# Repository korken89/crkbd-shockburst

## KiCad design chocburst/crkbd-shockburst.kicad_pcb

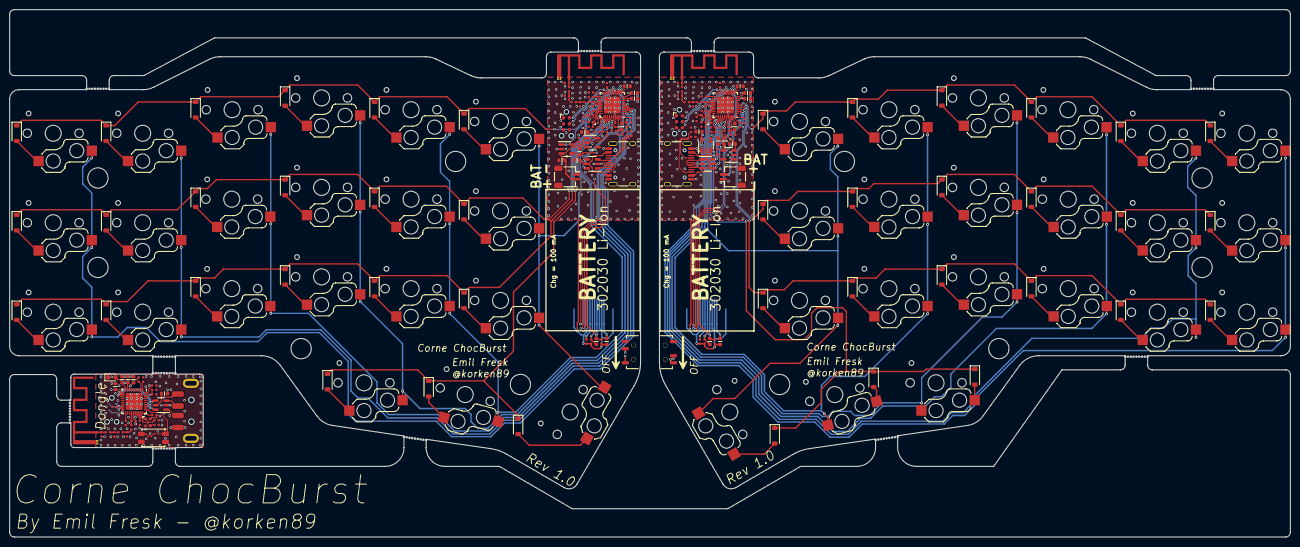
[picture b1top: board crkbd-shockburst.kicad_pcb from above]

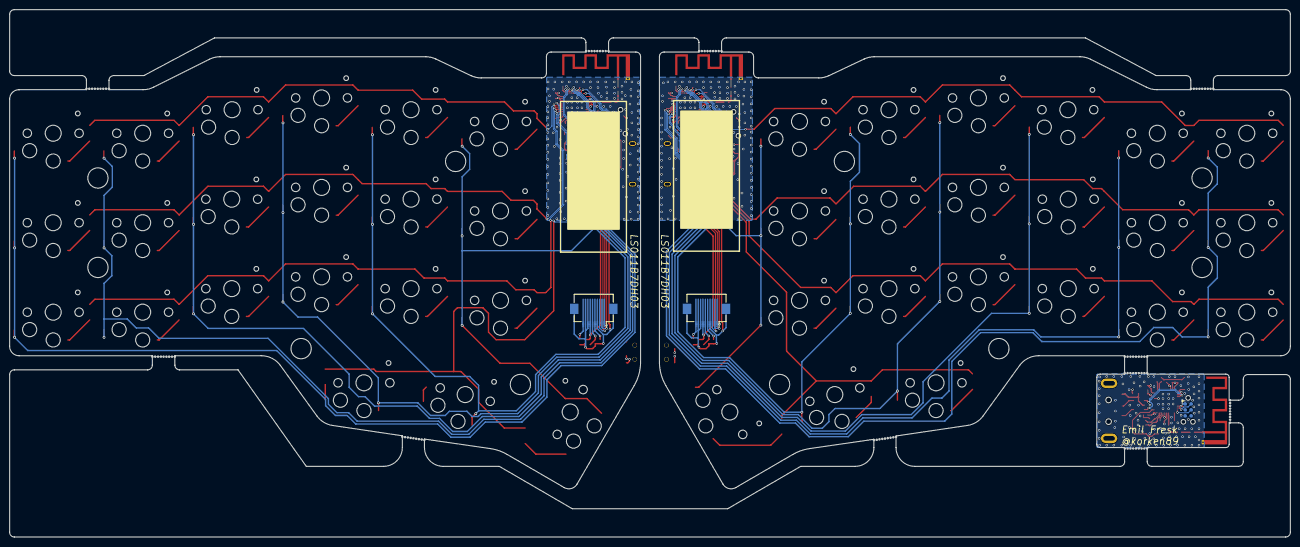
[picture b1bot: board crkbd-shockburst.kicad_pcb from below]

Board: 4 copper layers, 272.0 x 112.0 mm, 233 parts (3 on the bottom side), 157 nets.

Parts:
Ant101, Ant102, Ant601: antenna; Texas_SWRA117D_2.4GHz_Right
C201, C202, C206, C207, C208, C225, C503, C511, C512, C520, C521, C525, C603, C610, C611, C612: 4.7u; C_0603
C204, C209, C217, C218, C501, C509, C522, C523, C601, C609: 1u; C_0402
C205, C210, C211, C213, C219, C502, C504, C507, C508, C519, C602, C604, C607, C608: 100n; C_0402
C212, C505, C605: 100p; C_0402
C214, C506, C606: 820p; C_0402
C215, C216, C517, C518, C617, C618: 16p; C_0402
C220, C221, C513, C514, C613, C614: C_0402
C222, C515, C615: 1.2p; C_0402
C223, C516, C616: 1p; C_0402
C224, C524: 560p; C_0402
D301, D302, D303, D304, D305, D306, D307, D308, D309, D310, D311, D312, D313, D314, D315, D316, D317, D318, D319, D320, D321, D401, D402, D403, D404, D405, D406, D407, D408, D409, D410, D411, D412, D413, D414, D415, D416, D417, D418, D419, D420, D421: BAT43W; D_SOD-123
D601: RED; D_0603_1608Metric
FB201, FB202, FB203, FB501, FB502, FB503, FB601: FerriteBead_Small; R_0603
H201, H202, H203, H204, H205, H501, H502, H503, H504, H505: MountingHole; MountingHole_4.3mm_M4
J5, J5#2, J5#3, J5#4, J5#5, J5#6, J5#7, J5#8, J5#9, J5#10, J5#11: Breakaway_Tabs
J201, J502: USB_C_Receptacle_USB2.0; USB_C_Receptacle_USB4105
J202, J501, J601: tag-connect-swd; Tag-Connect_TC2030-IDC-NL_2x03_P1.27mm_Vertical
J203, J503: LCD; Hirose_FH12-10S-0.5SH_1x10-1MP_P0.50mm_Horizontal
J204, J504: Conn_01x02_MountingPin; JST_SH_SM02B-SRSS-TB_1x02-1MP_P1.00mm_Horizontal
J602: USB_A; USB_A_1001-011-01101
L201, L502: 10u; R_0603
L202, L501: 47n; R_0402
L203, L503, L603: R_0402
L204, L505, L605: 4.7n; R_0402
L205, L504, L604: 2.2n; R_0402
R101, R601: 1k; R_0402
R201, R202, R502, R503: 1M; R_0402
R203, R204, R504, R505: 5.1k; R_0402
R206, R506: 10k; R_0402
SW101, SW102: SW_SPDT; SSSS810701
SW301, SW302, SW303, SW304, SW305, SW306, SW307, SW308, SW309, SW310, SW311, SW312, SW313, SW314, SW315, SW316, SW317, SW318, SW319, SW320, SW401, SW402, SW403, SW404, SW405, SW406, SW407, SW408, SW409, SW410, SW411, SW412, SW413, SW414, SW415, SW416, SW417, SW418, SW419, SW420: SW_Push; Kailh Choc Hotswap 1U
SW321, SW421: SW_Push; Kailh Choc Hotswap 1.5U
SW601: SW_Push; SW_SPST_EVQP2
U201, U501, U601: nRF52833-QDxx; QFN-40-1EP_5x5mm_P0.4mm_EP3.6x3.6mm
U202, U502, U602: USBLC6-2SC6; SOT-23-6
U203, U504: TPS70630DBVR; SOT-23-5
U204, U503: MCP73832-2-OT; SOT-23-5
Y201, Y501, Y601: 32 MHz; Crystal_4Pin_2.0x1.6mm

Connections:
/Left Keyboard Controller/ANT1: C223.1, L204.2, U201.24 (ANT)
/Left Keyboard Controller/ANT2: C222.1, L204.1, L205.2
/Left Keyboard Controller/ANT3: C221.1, L203.2, L205.1
/Left Keyboard Controller/ANT4: Ant101.1, C220.1, L203.1
/Left Keyboard Controller/CC1: J201.A5 (CC1), R203.2
/Left Keyboard Controller/CC2: J201.B5 (CC2), R204.2
/Left Keyboard Controller/CHG_STAT: U201.17 (P0.20), U204.1 (STAT)
/Left Keyboard Controller/CS: J203.3, U201.36 (AIN7/P0.31)
/Left Keyboard Controller/D+: U201.13 (D+), U202.4 (I/O2)
/Left Keyboard Controller/D-: U201.12 (D-), U202.6 (I/O1)
/Left Keyboard Controller/DATA_IN: J203.2, U201.6 (P1.09)
/Left Keyboard Controller/DCC: L201.2, U201.39 (DCC)
/Left Keyboard Controller/DEC1: C211.1, U201.1 (DEC1)
/Left Keyboard Controller/DEC3: C212.1, U201.27 (DEC3)
/Left Keyboard Controller/DEC4_6: C204.1, C213.1, L202.1, U201.26 (DEC6), U201.38 (DEC4)
/Left Keyboard Controller/DEC5: C214.1, U201.21 (DEC5)
/Left Keyboard Controller/DECUSB: C208.1, U201.11 (DECUSB)
/Left Keyboard Controller/DISP: C224.1, J203.5
/Left Keyboard Controller/KIO0: D301.1 (K), D302.1 (K), D303.1 (K), D304.1 (K), D305.1 (K), D306.1 (K), U201.23 (NFC2/P0.10)
/Left Keyboard Controller/KIO1: D307.1 (K), D308.1 (K), D309.1 (K), D310.1 (K), D311.1 (K), D312.1 (K), U201.15 (P0.17)
/Left Keyboard Controller/KIO2: D313.1 (K), D314.1 (K), D315.1 (K), D316.1 (K), D317.1 (K), D318.1 (K), U201.14 (P0.15)
/Left Keyboard Controller/KIO3: D319.1 (K), D320.1 (K), D321.1 (K), U201.32 (AIN0/P0.02)
/Left Keyboard Controller/KIO4: SW301.1, SW307.1, SW313.1, U201.5 (AIN3/P0.05)
/Left Keyboard Controller/KIO5: SW302.1, SW308.1, SW314.1, U201.4 (AIN2/P0.04)
/Left Keyboard Controller/KIO6: SW303.1, SW309.1, SW315.1, U201.3 (XL2/P0.01)
/Left Keyboard Controller/KIO7: SW304.1, SW310.1, SW316.1, SW319.1, U201.35 (AIN6/P0.30)
/Left Keyboard Controller/KIO8: SW305.1, SW311.1, SW317.1, SW320.1, U201.34 (AIN5/P0.29)
/Left Keyboard Controller/KIO9: SW306.1, SW312.1, SW318.1, SW321.1, U201.33 (AIN4/P0.28)
/Left Keyboard Controller/LEFT: R101.2, U201.22 (NFC1/P0.09)
/Left Keyboard Controller/POWER_EN: SW101.1 (A), U203.3 (EN)
/Left Keyboard Controller/P_D+: J201.A6 (D+), J201.B6 (D+), U202.3 (I/O2)
/Left Keyboard Controller/P_D-: J201.A7 (D-), J201.B7 (D-), U202.1 (I/O1)
/Left Keyboard Controller/SCLK: J203.1, U201.2 (XL1/P0.00)
/Left Keyboard Controller/SWDCLK: J202.4 (SWCLK), U201.20 (SWDCLK)
/Left Keyboard Controller/SWDIO: J202.2 (SWDIO), U201.19 (SWDIO)
/Left Keyboard Controller/VBAT: C202.1, J204.2, R201.1, U203.1 (IN), U204.3 (V_{BAT})
/Left Keyboard Controller/VBAT_MEAS: C219.1, R201.2, R202.1, U201.31 (AIN1/P0.03)
/Left Keyboard Controller/VDD: C205.1, C206.1, C209.1, C210.1, C218.2, C225.1, FB202.1, J202.1 (VCC), J203.7, U201.8 (VDD), U201.9 (VDDH), U201.18 (VDD), U201.30 (VDD), U201.40 (VDD), U203.5 (OUT)
/Left Keyboard Controller/VDDA: C217.2, FB202.2, J203.6
/Left Keyboard Controller/VIN_USB: FB201.1, J201.A4 (VBUS), J201.A9 (VBUS), J201.B4 (VBUS), J201.B9 (VBUS), U202.5 (VBUS)
/Left Keyboard Controller/VSSA: FB203.2, J203.10
/Left Keyboard Controller/VUSB: C201.1, C207.1, FB201.2, U201.10 (VBUS), U204.4 (V_{DD})
/Left Keyboard Controller/XC1: C216.1, U201.28 (XC1), Y201.3
/Left Keyboard Controller/XC2: C215.1, U201.29 (XC2), Y201.1
/Right Keyboard Controller/ANT1: C516.1, L505.2, U501.24 (ANT)
/Right Keyboard Controller/ANT2: C515.1, L504.2, L505.1
/Right Keyboard Controller/ANT3: C514.1, L503.2, L504.1
/Right Keyboard Controller/ANT4: Ant102.1, C513.1, L503.1
/Right Keyboard Controller/CC1: J502.A5 (CC1), R505.2
/Right Keyboard Controller/CC2: J502.B5 (CC2), R504.2
/Right Keyboard Controller/CHG_STAT: U501.17 (P0.20), U503.1 (STAT)
/Right Keyboard Controller/CS: J503.3, U501.36 (AIN7/P0.31)
/Right Keyboard Controller/D+: U501.13 (D+), U502.4 (I/O2)
/Right Keyboard Controller/D-: U501.12 (D-), U502.6 (I/O1)
/Right Keyboard Controller/DATA_IN: J503.2, U501.6 (P1.09)
/Right Keyboard Controller/DCC: L502.2, U501.39 (DCC)
/Right Keyboard Controller/DEC1: C504.1, U501.1 (DEC1)
/Right Keyboard Controller/DEC3: C505.1, U501.27 (DEC3)
/Right Keyboard Controller/DEC4_6: C501.1, C502.1, L501.1, U501.26 (DEC6), U501.38 (DEC4)
/Right Keyboard Controller/DEC5: C506.1, U501.21 (DEC5)
/Right Keyboard Controller/DECUSB: C503.1, U501.11 (DECUSB)
/Right Keyboard Controller/DISP: C524.1, J503.5
/Right Keyboard Controller/KIO0: SW401.1, SW407.1, SW413.1, U501.23 (NFC2/P0.10)
/Right Keyboard Controller/KIO1: SW402.1, SW408.1, SW414.1, U501.15 (P0.17)
/Right Keyboard Controller/KIO2: SW403.1, SW409.1, SW415.1, U501.14 (P0.15)
/Right Keyboard Controller/KIO3: SW404.1, SW410.1, SW416.1, SW419.2, U501.32 (AIN0/P0.02)
/Right Keyboard Controller/KIO4: D401.1 (K), D402.1 (K), D403.1 (K), D404.1 (K), D405.1 (K), D406.1 (K), U501.5 (AIN3/P0.05)
/Right Keyboard Controller/KIO5: D407.1 (K), D408.1 (K), D409.1 (K), D410.1 (K), D411.1 (K), D412.1 (K), U501.4 (AIN2/P0.04)
/Right Keyboard Controller/KIO6: D413.1 (K), D414.1 (K), D415.1 (K), D416.1 (K), D417.1 (K), D418.1 (K), U501.3 (XL2/P0.01)
/Right Keyboard Controller/KIO7: D419.1 (K), D420.1 (K), D421.1 (K), U501.35 (AIN6/P0.30)
/Right Keyboard Controller/KIO8: SW406.1, SW412.1, SW418.1, SW421.2, U501.34 (AIN5/P0.29)
/Right Keyboard Controller/KIO9: SW405.1, SW411.1, SW417.1, SW420.2, U501.33 (AIN4/P0.28)
/Right Keyboard Controller/POWER_EN: SW102.3 (C), U504.3 (EN)
/Right Keyboard Controller/P_D+: J502.A6 (D+), J502.B6 (D+), U502.3 (I/O2)
/Right Keyboard Controller/P_D-: J502.A7 (D-), J502.B7 (D-), U502.1 (I/O1)
/Right Keyboard Controller/SCLK: J503.1, U501.2 (XL1/P0.00)
/Right Keyboard Controller/SWDCLK: J501.4 (SWCLK), U501.20 (SWDCLK)
/Right Keyboard Controller/SWDIO: J501.2 (SWDIO), U501.19 (SWDIO)
/Right Keyboard Controller/VBAT: C521.1, J504.2, R502.1, U503.3 (V_{BAT}), U504.1 (IN)
/Right Keyboard Controller/VBAT_MEAS: C519.1, R502.2, R503.1, U501.31 (AIN1/P0.03)
/Right Keyboard Controller/VDD: C507.1, C508.1, C509.1, C511.1, C523.2, C525.1, FB502.1, J501.1 (VCC), J503.7, U501.8 (VDD), U501.9 (VDDH), U501.18 (VDD), U501.30 (VDD), U501.40 (VDD), U504.5 (OUT)
/Right Keyboard Controller/VDDA: C522.2, FB502.2, J503.6
/Right Keyboard Controller/VIN_USB: FB501.1, J502.A4 (VBUS), J502.A9 (VBUS), J502.B4 (VBUS), J502.B9 (VBUS), U502.5 (VBUS)
/Right Keyboard Controller/VSSA: FB503.2, J503.10
/Right Keyboard Controller/VUSB: C512.1, C520.1, FB501.2, U501.10 (VBUS), U503.4 (V_{DD})
/Right Keyboard Controller/XC1: C517.1, U501.28 (XC1), Y501.3
/Right Keyboard Controller/XC2: C518.1, U501.29 (XC2), Y501.1
/USB Dongle/ANT1: C616.1, L605.2, U601.24 (ANT)
/USB Dongle/ANT2: C615.1, L604.2, L605.1
/USB Dongle/ANT3: C614.1, L603.2, L604.1
/USB Dongle/ANT4: Ant601.1, C613.1, L603.1
/USB Dongle/BUTTON: SW601.1, U601.31 (AIN1/P0.03)
/USB Dongle/D+: U601.13 (D+), U602.6 (I/O1)
/USB Dongle/D-: U601.12 (D-), U602.4 (I/O2)
/USB Dongle/DEC1: C604.1, U601.1 (DEC1)
/USB Dongle/DEC3: C605.1, U601.27 (DEC3)
/USB Dongle/DEC4_6: C601.1, C602.1, U601.26 (DEC6), U601.38 (DEC4)
/USB Dongle/DEC5: C606.1, U601.21 (DEC5)
/USB Dongle/DECUSB: C603.1, U601.11 (DECUSB)
/USB Dongle/LED: R601.2, U601.2 (XL1/P0.00)
/USB Dongle/P_D+: J602.3 (D+), U602.1 (I/O1)
/USB Dongle/P_D-: J602.2 (D-), U602.3 (I/O2)
/USB Dongle/SWDCLK: J601.4 (SWCLK), U601.20 (SWDCLK)
/USB Dongle/SWDIO: J601.2 (SWDIO), U601.19 (SWDIO)
/USB Dongle/VDD: C607.1, C608.1, C609.1, C610.1, J601.1 (VCC), U601.8 (VDD), U601.18 (VDD), U601.30 (VDD), U601.40 (VDD)
/USB Dongle/VIN_USB: FB601.1, J602.1 (VBUS), U602.5 (VBUS)
/USB Dongle/VUSB: C611.1, C612.1, FB601.2, U601.9 (VDDH), U601.10 (VBUS)
/USB Dongle/XC1: C617.1, U601.28 (XC1), Y601.3
/USB Dongle/XC2: C618.1, U601.29 (XC2), Y601.1
GND: Ant101.2, Ant102.2, Ant601.2, C201.2, C202.2, C204.2, C205.2, C206.2, C207.2, C208.2, C209.2, C210.2, C211.2, C212.2, C213.2, C214.2, C215.2, C216.2, C217.1, C218.1, C219.2, C220.2, C221.2, C222.2, C223.2, C224.2, C225.2, C501.2, C502.2, C503.2, C504.2, C505.2, C506.2, C507.2, C508.2, C509.2, C511.2, C512.2, C513.2, C514.2, C515.2, C516.2, C517.2, C518.2, C519.2, C520.2, C521.2, C522.1, C523.1, C524.2, C525.2, C601.2, C602.2, C603.2, C604.2, C605.2, C606.2, C607.2, C608.2, C609.2, C610.2, C611.2, C612.2, C613.2, C614.2, C615.2, C616.2, C617.2, C618.2, D601.1 (K), FB203.1, FB503.1, J201.A1 (GND), J201.A12 (GND), J201.B1 (GND), J201.B12 (GND), J201.S1 (SHIELD), J202.5 (GND), J203.4, J203.8, J203.9, J203.MP (MountPin), J204.1, J204.MP (MountPin), J501.5 (GND), J502.A1 (GND), J502.A12 (GND), J502.B1 (GND), J502.B12 (GND), J502.S1 (SHIELD), J503.4, J503.8, J503.9, J503.MP (MountPin), J504.1, J504.MP (MountPin), J601.5 (GND), J602.4 (GND), J602.5 (Shield), R101.1, R202.2, R203.1, R204.1, R206.1, R503.2, R504.1, R505.1, R506.1, SW101.2 (B), SW102.2 (B), SW601.2, U201.25 (VSS_PA), U201.37 (VSS), U201.41 (VSS), U202.2 (GND), U203.2 (GND), U204.2 (V_{SS}), U501.25 (VSS_PA), U501.37 (VSS), U501.41 (VSS), U502.2 (GND), U503.2 (V_{SS}), U504.2 (GND), U601.25 (VSS_PA), U601.37 (VSS), U601.41 (VSS), U602.2 (GND), Y201.2, Y201.4, Y501.2, Y501.4, Y601.2, Y601.4
unnamed: D301.2 (A), SW301.2
unnamed: D302.2 (A), SW302.2
unnamed: D303.2 (A), SW303.2
unnamed: D304.2 (A), SW304.2
unnamed: D305.2 (A), SW305.2
unnamed: D306.2 (A), SW306.2
unnamed: D307.2 (A), SW307.2
unnamed: D308.2 (A), SW308.2
unnamed: D309.2 (A), SW309.2
unnamed: D310.2 (A), SW310.2
unnamed: D311.2 (A), SW311.2
unnamed: D312.2 (A), SW312.2
unnamed: D313.2 (A), SW313.2
unnamed: D314.2 (A), SW314.2
unnamed: D315.2 (A), SW315.2
unnamed: D316.2 (A), SW316.2
unnamed: D317.2 (A), SW317.2
unnamed: D318.2 (A), SW318.2
unnamed: D319.2 (A), SW319.2
unnamed: D320.2 (A), SW320.2
unnamed: D321.2 (A), SW321.2
unnamed: D401.2 (A), SW401.2
unnamed: D402.2 (A), SW402.2
unnamed: D403.2 (A), SW403.2
unnamed: D404.2 (A), SW404.2
unnamed: D405.2 (A), SW405.2
unnamed: D406.2 (A), SW406.2
unnamed: D407.2 (A), SW407.2
unnamed: D408.2 (A), SW408.2
unnamed: D409.2 (A), SW409.2
unnamed: D410.2 (A), SW410.2
unnamed: D411.2 (A), SW411.2
unnamed: D412.2 (A), SW412.2
unnamed: D413.2 (A), SW413.2
unnamed: D414.2 (A), SW414.2
unnamed: D415.2 (A), SW415.2
unnamed: D416.2 (A), SW416.2
unnamed: D417.2 (A), SW417.2
unnamed: D418.2 (A), SW418.2
unnamed: D419.2 (A), SW419.1
unnamed: D420.2 (A), SW420.1
unnamed: D421.2 (A), SW421.1
unnamed: D601.2 (A), R601.1
unnamed: L201.1, L202.2
unnamed: L501.2, L502.1
unnamed: R206.2, U204.5 (PROG)
unnamed: R506.2, U503.5 (PROG)

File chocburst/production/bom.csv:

Designator,Footprint,Quantity,Value,LCSC Part #
"C201, C202, C206, C207, C208, C225, C503, C511, C512, C520, C521, C525, C603, C610, C611, C612",C_0603,16,4.7u,C961503
"C204, C209, C217, C218, C501, C509, C522, C523, C601, C609",C_0402,10,1u,C525327
"C205, C210, C211, C213, C219, C502, C504, C507, C508, C519, C602, C604, C607, C608",C_0402,14,100n,C2874742
"C212, C505, C605",C_0402,3,100p,C327785
"C214, C506, C606",C_0402,3,820p,C147541
"C215, C216, C517, C518, C617, C618",C_0402,6,16p,C396888
"C220, C221, C513, C514, C613, C614",C_0402,6,~,
"C222, C515, C615",C_0402,3,1.2p,C363514
"C223, C516, C616",C_0402,3,1p,C363513
"C224, C524",C_0402,2,560p,C363544
"D301, D302, D303, D304, D305, D306, D307, D308, D309, D310, D311, D312, D313, D314, D315, D316, D317, D318, D319, D320, D321, D401, D402, D403, D404, D405, D406, D407, D408, D409, D410, D411, D412, D413, D414, D415, D416, D417, D418, D419, D420, D421",D_SOD-123,42,BAT43W,C130885
D601,0603,1,RED,C497930
"FB201, FB202, FB203, FB501, FB502, FB503, FB601",R_0603,7,FerriteBead_Small,C275454
"J201, J502",USB_C_Receptacle_USB4105,2,USB_C_Receptacle_USB2.0,C165948
"J203, J503",Hirose_FH12-10S-0.5SH_1x10-1MP_P0.50mm_Horizontal,2,LCD,C2919556
"J204, J504",JST_SH_SM02B-SRSS-TB_1x02-1MP_P1.00mm_Horizontal,2,Conn_01x02_MountingPin,
"J5_11, J5_10, J5_9, J5_8, J5_7, J5_6, J5_5, J5_4, J5_3, J5_2, J5",Breakaway_Tabs,11,Breakaway_Tabs,
J602,USB_A_1001-011-01101,1,USB_A,
"L201, L502",R_0603,2,10u,
"L202, L501",R_0402,2,47n,
"L203, L503, L603",R_0402,3,~,
"L204, L505, L605",R_0402,3,4.7n,C304335
"L205, L504, L604",R_0402,3,2.2n,C918998
"R101, R601",R_0402,2,1k,C258117
"R201, R202, R502, R503",R_0402,4,1M,C364860
"R203, R204, R504, R505",R_0402,4,5.1k,C188116
"R206, R506",R_0402,2,10k,C144807
"SW101, SW102",SSSS810701,2,SW_SPDT,C97433
"SW301, SW302, SW303, SW304, SW305, SW306, SW307, SW308, SW309, SW310, SW311, SW312, SW313, SW314, SW315, SW316, SW317, SW318, SW319, SW320, SW401, SW402, SW403, SW404, SW405, SW406, SW407, SW408, SW409, SW410, SW411, SW412, SW413, SW414, SW415, SW416, SW417, SW418, SW419, SW420",Kailh Choc Hotswap 1U,40,SW_Push,C5333465
"SW321, SW421",Kailh Choc Hotswap 1.5U,2,SW_Push,C5333465
SW601,SW_SPST_EVQP2,1,SW_Push,
"U201, U501, U601",QFN-40-1EP_5x5mm_P0.4mm_EP3.6x3.6mm,3,nRF52833-QDxx,C2895249 or C3007767
"U202, U502, U602",SOT-23-6,3,USBLC6-2SC6,C7519
"U203, U504",SOT-23-5,2,TPS70630DBVR,C2859817
"U204, U503",SOT-23-5,2,MCP73832-2-OT,C38066
"Y201, Y501, Y601",Crystal_4Pin_2.0x1.6mm,3,32 MHz,C648961

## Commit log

2023-08-06 Initial project
2023-08-06 Schematics
2023-08-08 Layout
2023-08-09 Add top/bottom plate
2023-08-09 Production files
2023-08-12 Make hotswap sockets mountable by JLCPCB
2023-08-13 Save
2023-08-13 Testing memory pixel display
2023-08-19 Finished routing, passing DRC
2023-08-20 Cleanup
2023-08-20 Add power switch
2023-08-20 Started firmware
2023-08-22 Reorganization, added dongle firmware folder
2023-08-24 Radio test working
2023-08-24 Testing other radio settings
2023-08-26 Some small fixes for battery connector
2023-08-27 Async RX and TX working
2023-08-28 2 MBit mode seems to work
2023-09-01 Fix radio sometimes panicing
2023-09-01 Add Chocolate switch version
2023-09-17 Update top plate
2023-09-17 Test time sync TX
2023-09-23 Save testing ack
2023-10-08 Testing channel hopping and listening for packets
2023-10-08 Some packets are getting through :)
2023-10-09 Make sure RX is of before switching channel frequency
2023-10-10 Testing ECDH, added docs for connection protocol
2023-10-11 Abstract slot size
2023-10-15 Save docs and new channel hopping sequence
2023-10-17 Less logging, added testing features
2023-10-17 Add testing commands to readme
2023-10-18 Fix time estimates for keygen and sign/verify
2023-10-24 Testing p256, x25519, aes, chacha20poly1305
2023-10-25 Test salty
